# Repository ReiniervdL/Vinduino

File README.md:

# Vinduino

The Vinduino project started from the necessity to manage irrigation in my small Southern California vineyard, by monitoring soil moisture at different depths and at several vineyard locations. 
Soil moisture monitoring systems have been around for decades, but they cost hundreds to thousands of dollars and -because these systems are proprietary- there will be ongoing cost to customize and maintain these systems. As a small vineyard owner, I needed something low cost and flexible.
The open source Arduino platform, together with low cost gypsum soil moisture and salinity sensors, provides all that. While I first envisioned the Vinduino project (Vineyard + Arduino) for my personal interest and needs, but now the scope has broadened to providing easy to use, open source, low cost solutions for agricultural irrigation management.

Saving water is more important now than ever. The four year drought in California made everybody realize the importance of reducing water use. But it is not just California that is plagued by prolonged drought periods. Large agricultural areas in South America, India, China, and Africa suffer from continuing water shortage as well.

The Vinduino project provided the following results, published on the Vinduino blog, Hackaday, and Github:

* DIY calibrated gypsum soil moisture sensors (Watermark SS200 is also supported)
* Hand held sensor reader (soil moisture, soil/water salinity, water pressure)
* Solar powered remote sensor platform (Vinduino R3), available on Tindie.com
	Options include:
	4 electrically separated inputs for soil moisture sensors
	Wifi (ESP8266), Globalsat LM-210 private LoRa network module, Globalsat LM-513 module for LoRaWAN (The Things Network)
	Irrigation valve control, optional pressure sensor for valve operation feedback
	several options for temperature/humidity sensors
	Built in solar battery charger
	Built in real time clock for precise irrigation timing
* Gateway to connect multiple LoRa end nodes to the Internet via Wifi (Vinduino Gateway)

All publicly released programming and documentation is available for free under the GNU General Public License 3.0.

For non-DIY we offer commercial products at www.vinduino.com and https://www.amazon.com/Vinduino-Agricultural-Irrigation-Monitoring-Starter/dp/B0828JCK49

Support web site: https://vinduino.freshdesk.com/support/home

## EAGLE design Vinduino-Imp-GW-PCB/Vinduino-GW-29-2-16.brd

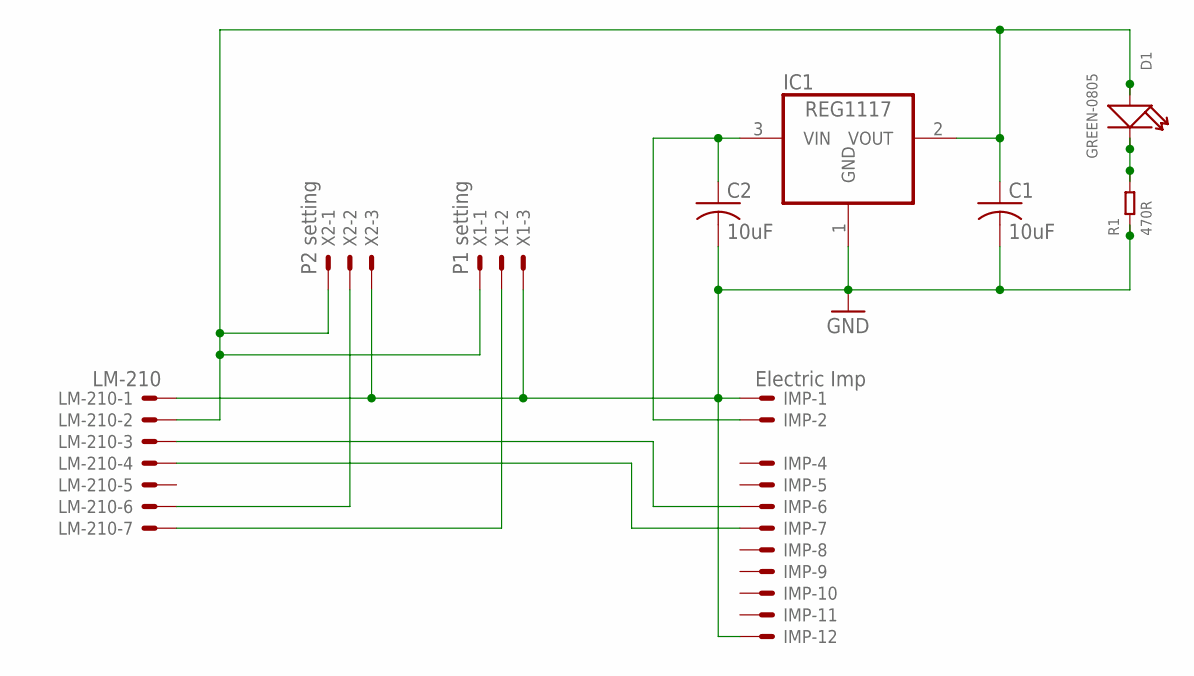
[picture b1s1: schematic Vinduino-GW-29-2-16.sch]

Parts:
C1, C2: 10uF; C025-030X050
D1: GREEN-0805; LED-0805
IC1: REG1117; SOT223
IMP: Electric Imp; 22-23-2121
LM-210: LM-210; 22-23-2071
R1: 470R; R0805
X1: P1 setting; 22-23-2031
X2: P2 setting; 22-23-2031

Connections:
GND: C1.2, C2.2, IC1.1 (GND), IMP.1, IMP.12, LM-210.1, R1.1, X1.3, X2.3
unnamed: C2.1, IC1.3 (VIN), IMP.2
unnamed: LM-210.6, X2.2
unnamed: LM-210.7, X1.2
unnamed: IMP.6, LM-210.3
unnamed: IMP.7, LM-210.4
unnamed: D1.-, R1.2
unnamed: C1.1, D1.+, IC1.2 (VOUT), LM-210.2, X1.1, X2.1

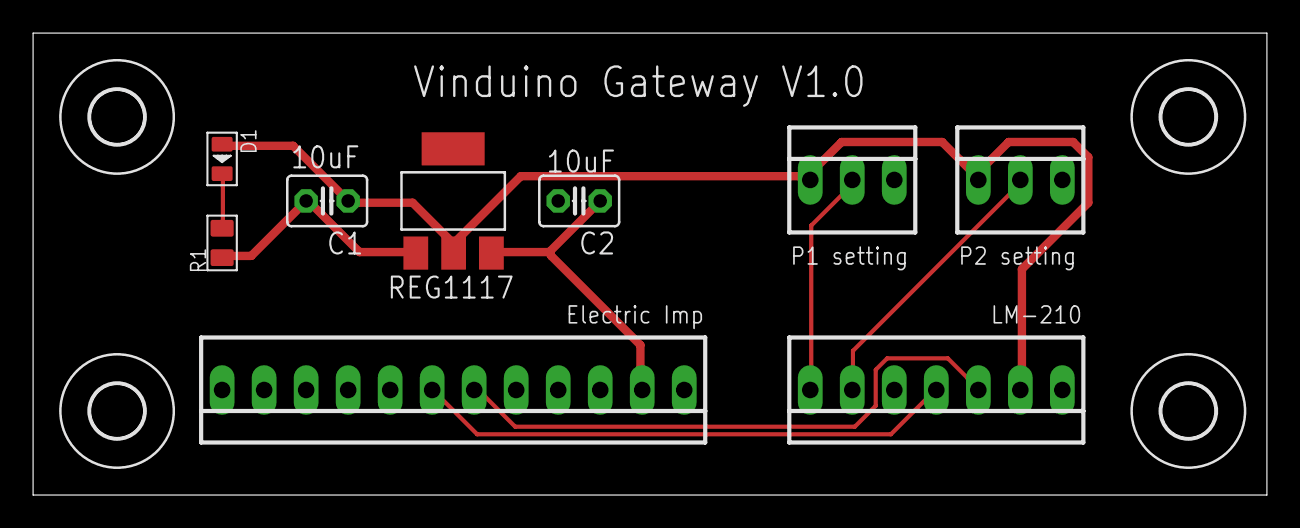
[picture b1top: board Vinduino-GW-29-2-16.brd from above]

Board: 2 copper layers, 74.6 x 27.9 mm, 13 parts (0 on the bottom side), 8 nets.

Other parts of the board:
U$1, U$2, U$3, U$4: 3,2

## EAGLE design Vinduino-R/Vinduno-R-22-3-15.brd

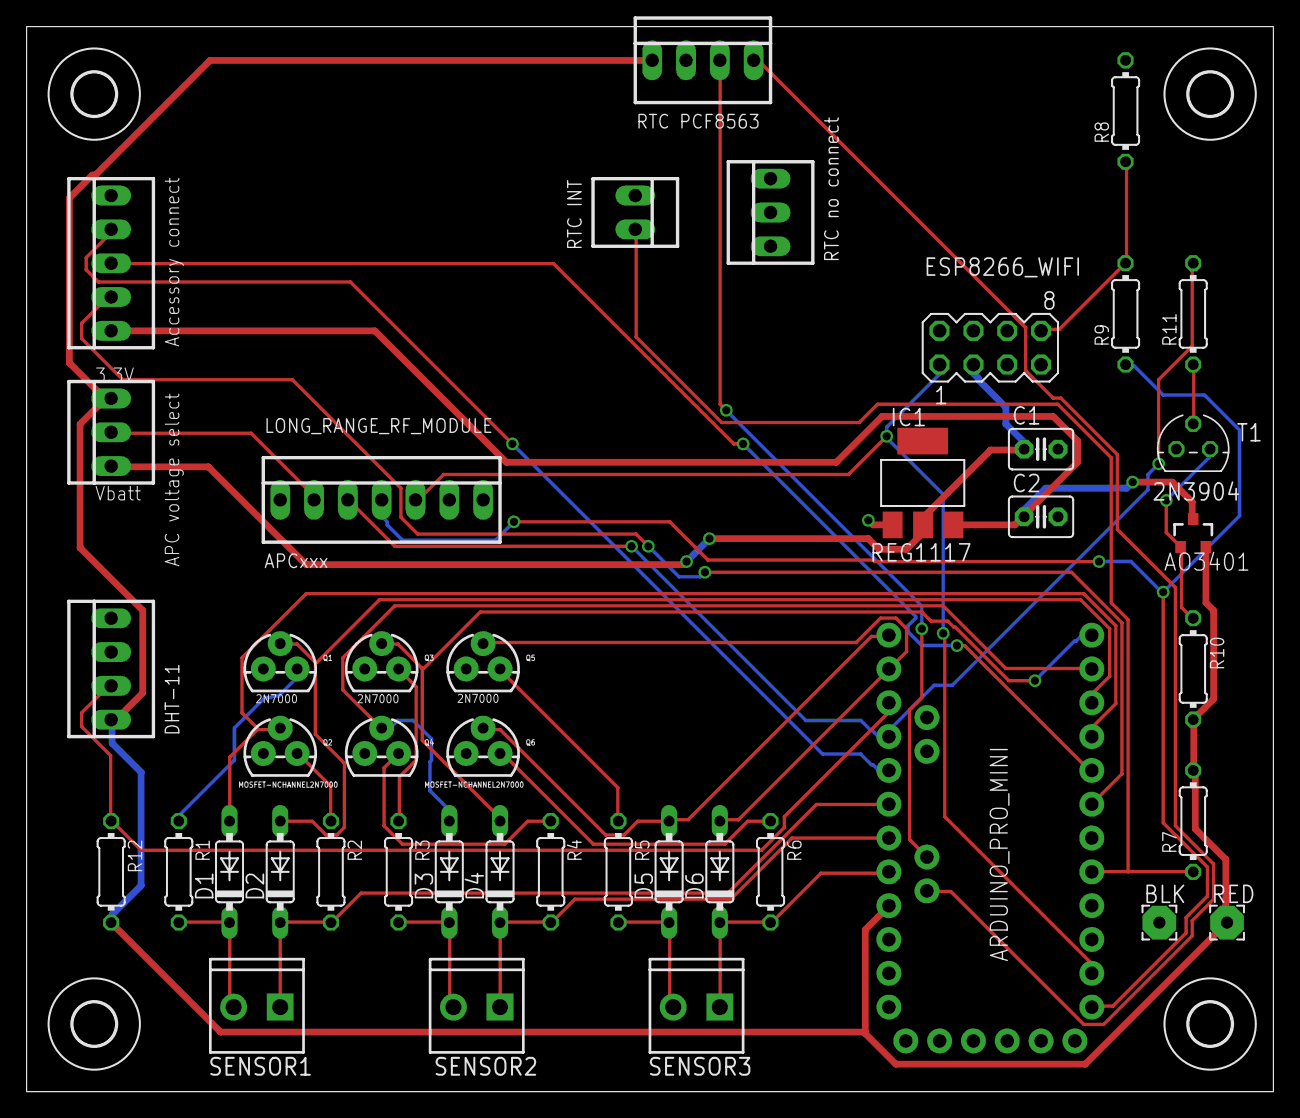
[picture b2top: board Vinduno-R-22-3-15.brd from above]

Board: 2 copper layers, 93.7 x 80.0 mm, 47 parts (0 on the bottom side), 36 nets.

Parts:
ACC: Accessory connect; 22-23-2051
BLK: 2,54/0,9
C1, C2: 1uF; C025-030X050
D1, D2, D3, D4, D5, D6: 1N4148DO35-7; DO35-7
DHT: DHT-11; 22-23-2041
ESP8266_WIFI: WiFi; MA04-2
IC1: REG1117; SOT223
LONG_RANGE_RF_MODULE: APCxxx; 22-23-2071
MCU: ARDUINO_PRO_MINI
Q1, Q3, Q5: 2N7000; TO-92
Q2, Q4, Q6: MOSFET-NCHANNEL2N7000; TO-92
Q7: AO3401; SOT23-3
R1, R2, R3, R4, R5, R6, R7: 4k7; 0204/7
R8, R10: 10k; 0204/7
R9, R12: 3k3; 0204/7
R11: 22k; 0204/7
RED: 2,54/0,9
RTC: RTC PCF8563; 22-23-2041
RTC_INT: RTC INT; 22-23-2021
RTC_NC: RTC no connect; 22-23-2031
SENSOR1: Sensor 1; SCREWTERMINAL-3.5MM-2
SENSOR2, SENSOR3: M023.5MM; SCREWTERMINAL-3.5MM-2
T1: 2N3904; TO92
U$1, U$2, U$3, U$4: 3,2
X2: 22-23-2031

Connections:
+5V: DHT.1, MCU.21, Q7.2, R7.2, R10.2, R12.2, RED.1, RTC.1, X2.3
+5V/2: ACC.1, C2.1, IC1.3, Q7.3
DIODE1: D1.A, MCU.9, Q2.2
DIODE2: D2.A, MCU.10, Q1.2
DIODE3: D3.A, MCU.11, Q4.2
DIODE4: D4.A, MCU.12, Q3.2
DIODE5: D5.A, MCU.13, Q6.2
DIODE6: D6.A, MCU.14, Q5.2
GND: ACC.5, BLK.1, C1.2, C2.2, DHT.4, ESP8266_WIFI.2, IC1.1, LONG_RANGE_RF_MODULE.1, MCU.4, MCU.23, Q1.1, Q2.1, Q3.1, Q4.1, Q5.1, Q6.1, R8.2, RTC.2, T1.3
unnamed: D1.C, R1.2, SENSOR1.2
unnamed: D2.C, MCU.18, R2.2, SENSOR1.1
unnamed: D3.C, R3.2, SENSOR2.2
unnamed: D4.C, MCU.19, R4.2, SENSOR2.1
unnamed: Q1.3, R1.1
unnamed: D5.C, R5.2, SENSOR3.2
unnamed: D6.C, MCU.20, R6.2, SENSOR3.1
unnamed: ACC.4, MCU.17
unnamed: MCU.A4, RTC.3
unnamed: LONG_RANGE_RF_MODULE.3, MCU.16, R11.2
unnamed: LONG_RANGE_RF_MODULE.4, MCU.1, R9.1
unnamed: ESP8266_WIFI.1, LONG_RANGE_RF_MODULE.5, MCU.2
unnamed: MCU.A5, RTC.4
unnamed: Q2.3, R2.1
unnamed: Q3.3, R3.1
unnamed: Q4.3, R4.1
unnamed: Q5.3, R5.1
unnamed: Q6.3, R6.1
unnamed: ESP8266_WIFI.8, R8.1, R9.2
unnamed: DHT.2, MCU.15, R12.1
unnamed: ACC.3, MCU.8
unnamed: Q7.1, R10.1, T1.1
unnamed: R11.1, T1.2
unnamed: MCU.5, R7.1, RTC_INT.2
unnamed: ACC.2, MCU.7
unnamed: C1.1, ESP8266_WIFI.3, IC1.2, X2.1
unnamed: LONG_RANGE_RF_MODULE.2, X2.2

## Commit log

2015-06-07 Create Vinduino-R_Wifi_V1.0
    Remote soil moisture 3-sensor node based on Vinduino-H V3
    Using ESP2866 Wifi module and PCF8563 RTC
    Using latest DHT libaray, allowing use of DHT11 or DHT 22
    Added galvanic voltage bias compensation
2015-06-07 Create Vinduino-R_sensor_test
    This sketch can be used to test the 3 sensor inputs, and can also be used to demonstrate bias errors caused by galvanic voltages generated by the sensors. This sketch does not work with ESP8266 insta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
    Arduino analog inputs A0, A6, and A7 need to be connected.
2015-06-07 Rename Vinduino-R_sensor_test to Vinduino-R_sensor_test.ino
2015-06-07 Create water_pressure_logger.ino
    This project requires three main components: an Arduino Uno board, an Adafruit data logger shield, and a 200 PSI pressure transducer (Eyourlife Universal 200PSI Pressure Transducer Sender Solenoid fo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
    See for transducer also: http://www.vanderleevineyard.com/1/post/2015/03/vinduino-water-pressure-meter.html
2015-06-07 Create Irrigation_valve_control.ino
    Hunter Sprinkler ICV201GDC ICV irrigation control valves can optionally use a DC latching solenoid (Hunter Sprinkler 458200 DC Latching Solenoid) for operation with a battery operated operated (Hunte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
    The latching solenoid can easily be driven with an Arduino board and a low cost motor driver module like L9110S DC Stepper Motor Driver Module H Bridge, available on-line for less than $6.
    The module needs 2 digital control lines (Arduino pin 13: latching on, and pin 12: latching off) per solenoid. The L9110S is a dual motor driver, so 2 valves can be controlled by one single module.
    The solenoid needs 9V to operate, a small battery pr
2015-06-07 Create water_pressure_meter.ino
    Here's code for a digital water pressure meter, based on the Arduino Pro Mini micro controller board, and the Vinduino-H PCB.
    The used pressure sensor is a $20 device, available on-line. It has a stainless steel housing and comes complete with a watertight connection cable. There are several ranges available. We purchased t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
    This sensor gives an output voltage between 0.5V and 4.5V that scales linearly with the measured pressure, 50 psi per volt.
    Hooking the sensor up to the Arduino board is easy. Only 3 wires are required: 5V supply (connect to Arduino Vcc pin), ground, and
2015-06-08 Vinduino-R picture
    Vinduino-R with APC220 RF module.
2015-07-02 Vinduino Eagle files
2015-10-06 Small change.
    Well done!!! Love the Gypsum Moisture sensor... :)
2015-10-17 adding conductivity measurement
2015-10-18 updated 10/17/2015
2016-03-21 Next generation Vinduino added
    Added option for LoRa long range networking and several improvements
2016-05-02 BOM
    Components listing
2016-07-30 Manual
    Vinduino R3 remote sensor station manual
2016-08-04 User manual update
    Added sensor calibration chart
2016-08-04 LoRa spec sheet
    Adding LM-210 LoRa module spec sheet
2016-08-10 Lora module design guide
2016-08-10 type corrected
2016-09-11 Test program
    Test program that comes pre-installed on the Vinduino board. Serial
    data output of resistance values measured at the soil sensor inputs
    every 3 seconds
2016-09-11 Program connector
    LoRa module IO is 3.3V. Do not connect when programming the Arduino to
    avoid 5V on LoRa module IOlines.
2016-09-24 Create Gateway-agent-code
    Vinduino LoRa LAN gateway code for the Electric Imp. Enter this in the left side editor window (agent code).
    Originally developed by Luke Beno, changed for ThingSpeak support. Provided under the GNU General Public License
2016-09-24 Create Gateway-device-code
    Vinduino LoRa LAN gateway code for the Electric Imp. Enter this in the right side editor window (device code).
    Originally developed by Luke Beno, changed for ThingSpeak support. Provided under the GNU General Public License
2016-12-11 Python based Vinduino gateway
    Python support for Globalsat LD-20 USB dongle
2017-02-04 Removed old ESP8266 code and replaced with version for R3
2017-02-04 clean up, added WiFi code
2017-03-08 Update March 2017
2017-08-06 Added conversions to Watermark Sensors
    Direct calculation to watermark kPa instead of the % moisture, as % moisture is dependant on soil type and less useful for varying conditions. All calculations taken directly from: https://www.kimber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
2018-03-10 Updates 3-10-18
    Updates and added support for FDR sensor
2019-03-12 LoRaWAN support
    Adding workshop slide deck and datasheet for LM-110/LM-130 for LoRaWAN support
2019-09-29 LM-210 and LD-20 configuration tool
2020-03-01 Added bOM
    Vinduino R3 bill of materials
2020-03-01 Add TTN LoRaWan support
    Added support for LoRaWAN (The Things Network) using Globalsat LM-513 module. This code is for the USA frequencies.
2020-06-20 Chirpstack + ham radio update
    Chirpstack database backup and ham radio CW Arduino keyer added
2020-07-12 Ham Radio section
    Separate section added for ham radio projects
2021-02-27 If humidity sensor is not connected default to 0. Otherwise the default value is -999 which fails to convert to HEX nicely.
2021-02-27 Add DevEui to allow connection to The Things Network

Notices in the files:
parts and their libraries:
SparkFun-Boards: Licensing: Creative Commons ShareAlike 4.0 International - https://creativecommons.org/licenses/by-sa/4.0
